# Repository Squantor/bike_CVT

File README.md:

# Bicycle Continuously Variable Transmission
This repository contains a the mechanics electronics and software for a CVT gearing system designed for bicycles.
This project is very much a work in progress
## Structure
* [electronics](electronics/README.md) contains all the electronic design files.
* [software](software/README.md) contains all the software.
* [mechanical](mechanical/README.md) contains all mechanical design files.
* [documentation](documentation/index.md) contains all project documentation, logs, research, papers, datasheets and more.
## Cloning
This repository makes use of submodules, use ```git clone --recurse-submodules https://github.com/Squantor/bike_CVT.git``` to clone everything in one go.

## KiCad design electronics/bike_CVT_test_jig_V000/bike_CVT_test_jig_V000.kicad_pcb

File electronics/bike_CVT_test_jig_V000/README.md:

# Bike CVT Test jig Verion 0
This is the Bike CVT project testing jig.
# HSI (Hardware Software Interface)
TODO: Stepper drive, limit switches, ADC inputs
## TODO's
Still some things need to be done:
* schematic entry 
* PCB layout
* Review with one night in between
* Produce
* Assemble
* Test & characterise
* update Readme.md with pictures and BOM
## BOM
TODO: Stepstick types

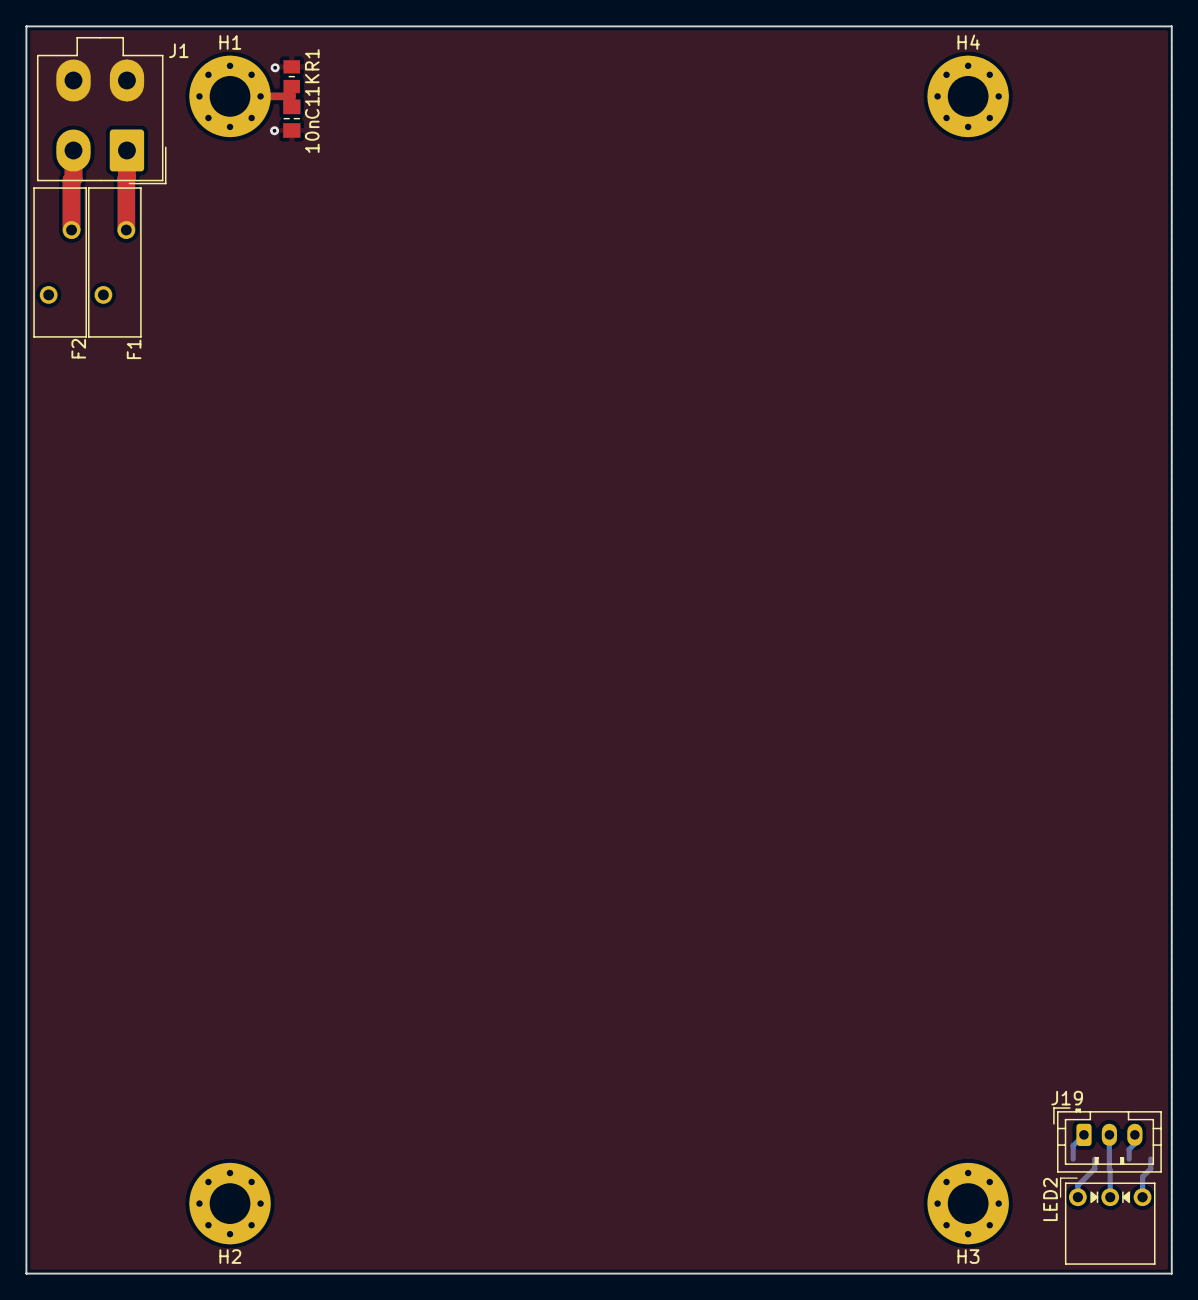
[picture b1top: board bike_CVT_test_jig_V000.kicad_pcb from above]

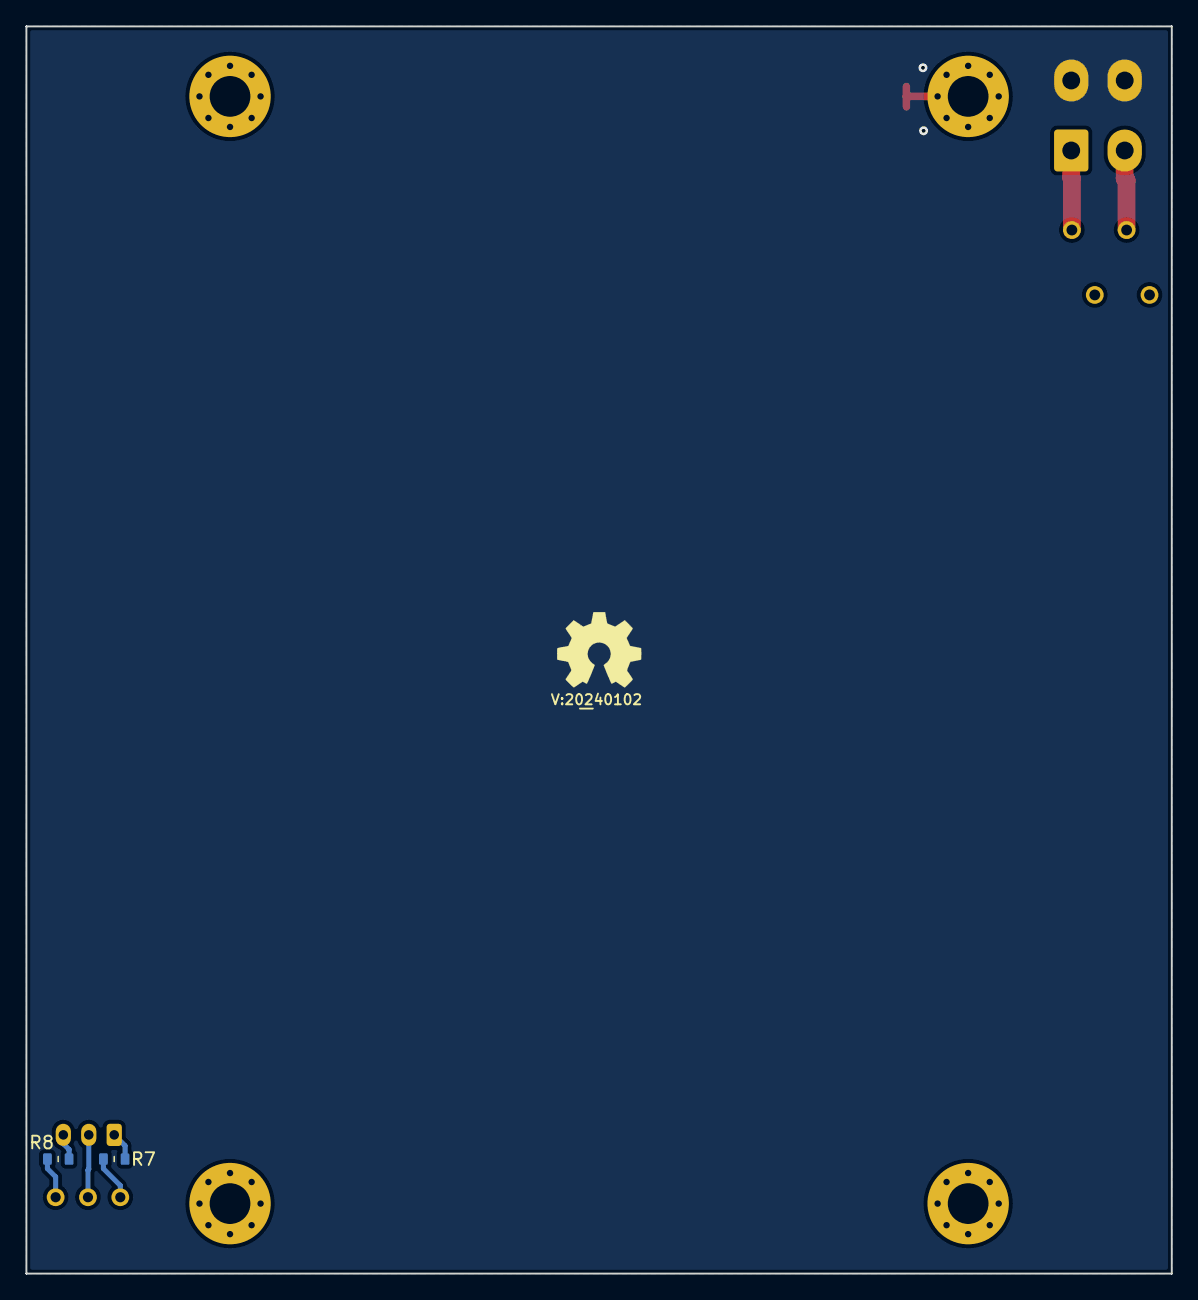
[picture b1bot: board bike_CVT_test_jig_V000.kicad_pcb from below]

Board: 2 copper layers, 90.0 x 98.0 mm, 15 parts (4 on the bottom side), 9 nets.

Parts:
C1: 10n; C_0805+0603
F1, F2: Fuse; Fuse_BelFuse_0ZRE0033FF_L11.4mm_W3.8mm
H1, H2, H3, H4: M3; MountingHole_3.2mm_M3_Pad_Via
J1: Conn_02x02_Counter_Clockwise; Molex_Mini-Fit_Jr_5566-04A_2x02_P4.20mm_Vertical
J19: Conn_01x03; JST_PH_B3B-PH-K_1x03_P2.00mm_Vertical
LED2: LED_Dual_CC; LED_DUAL_TH245_90deg
N1: OHWLOGO; OSHW-Symbol_6.7x6mm_SilkScreen
N2: V:20240102; Label_Generic
R1: 1K; R_0805+0603
R7, R8: R; R_0603_hand

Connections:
GND: C1.2, J1.3, J1.4, R1.2
unnamed: C1.1, H1.1, R1.1
unnamed: F1.2, J1.1
unnamed: F2.2, J1.2
unnamed: J19.1, R7.2
unnamed: J19.2, LED2.2 (C)
unnamed: J19.3, R8.2
unnamed: LED2.1 (A1), R7.1
unnamed: LED2.3 (A2), R8.1

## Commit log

2023-11-03 loading up first documentation tree
2023-11-03 updated gitignore with newer freecad gitignores
2023-11-03 started by adding motor mount for the test jig
2023-11-03 added ring gear bearing mount
2023-11-03 changed ring gear bearing completely
2023-11-04 made mount thinner to allow more space for motor axle
2023-11-04 ring gear in progress
2023-11-05 completed ring gear model
2023-11-05 fixed timing belt parametric calculations
2023-11-05 small fine tuning of dimensions
2024-01-02 small changes in ring gear
2024-01-02 added pcb library
2024-01-02 initial bike CVT test jig V0
2024-01-02 added kicad 7 temporary files
2024-01-02 added power connectors
2024-01-03 schematic entry work in progress
2024-01-03 added pi pico kicad library
2024-01-03 added some pins to stepstick, added pi pico library, updated PCB library
